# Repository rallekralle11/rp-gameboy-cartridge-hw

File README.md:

I had the idea to add the option to mount the USB port completely internally as well so it looks more "elegant".

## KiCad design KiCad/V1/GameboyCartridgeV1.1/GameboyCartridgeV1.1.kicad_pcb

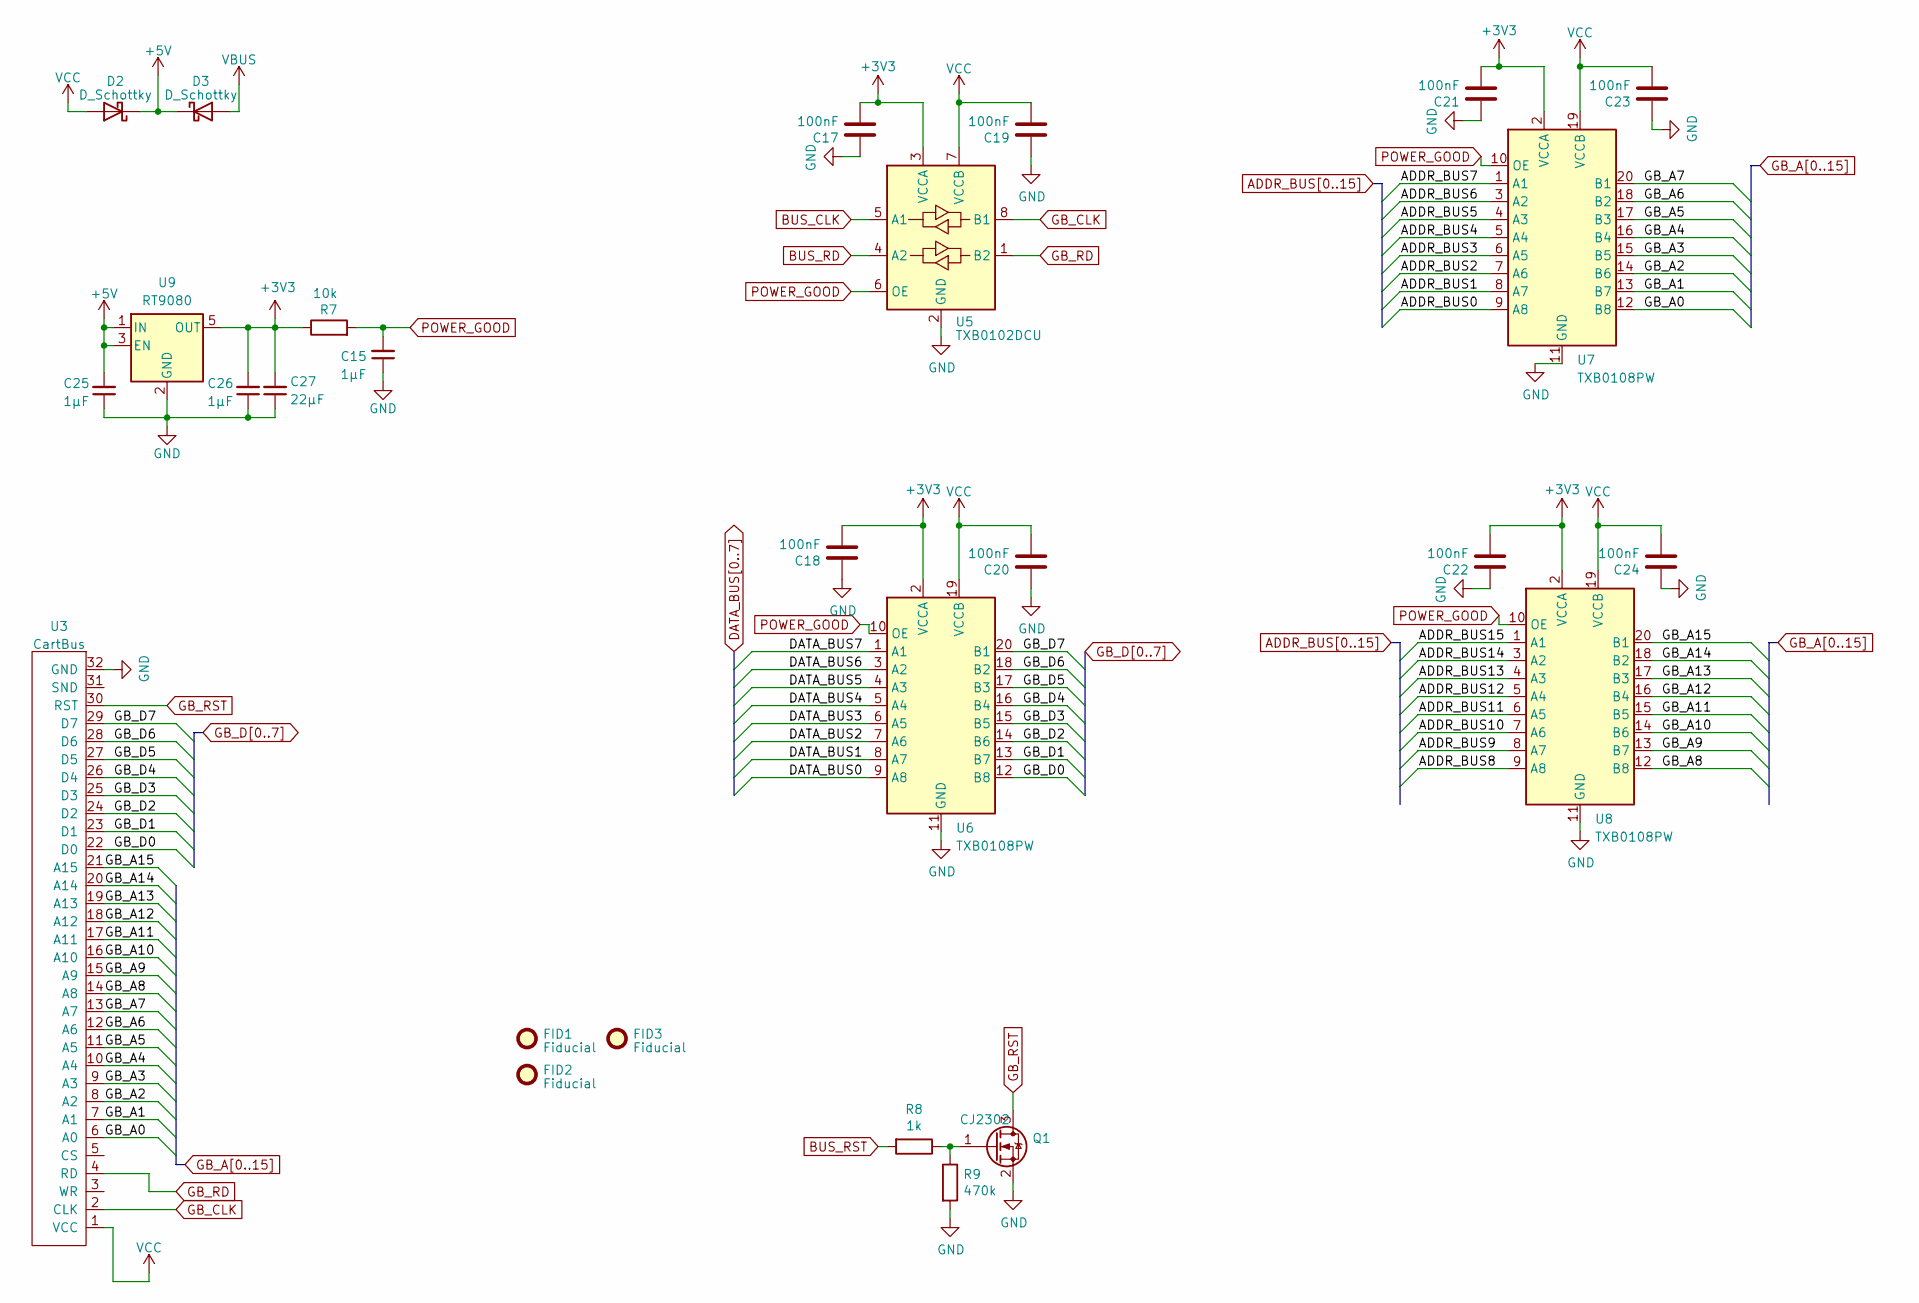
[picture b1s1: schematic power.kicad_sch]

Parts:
C15, C25, C26: 1µF; C_0603_1608Metric_Pad1.08x0.95mm_HandSolder
C17, C18, C19, C20, C21, C22, C23, C24: 100nF; C_0603_1608Metric_Pad1.08x0.95mm_HandSolder
C27: 22µF; C_0805_2012Metric
D2, D3: D_Schottky; D_SOD-323; LCSC C669022
FID1, FID2, FID3: Fiducial; Fiducial_1mm_Mask2mm
Q1: CJ2302; SOT-23_Handsoldering; LCSC C8548
R7: 10k; R_0603_1608Metric_Pad0.98x0.95mm_HandSolder
R8: 1k; R_0603_1608Metric_Pad0.98x0.95mm_HandSolder
R9: 470k; R_0603_1608Metric_Pad0.98x0.95mm_HandSolder
U3: CartBus; GameBoy_Cartridge_EdgeConnector
U5: TXB0102DCU; VSSOP-8_2.4x2.1mm_P0.5mm; LCSC C60709
U6, U7, U8: TXB0108PW; TSSOP-20_4.4x6.5mm_P0.65mm; LCSC C53406
U9: RT9080; SOT-23-5

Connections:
+3V3: C17.2, C18.2, C21.2, C22.2, C26.2, C27.2, R7.1, U5.3 (VCCA), U6.2 (VCCA), U7.2 (VCCA), U8.2 (VCCA), U9.5 (OUT); also elsewhere on the board
+5V: C25.2, D2.1 (K), D3.1 (K), U9.1 (IN), U9.3 (EN)
ADDR_BUS0: U7.9 (A8); also elsewhere on the board
ADDR_BUS1: U7.8 (A7); also elsewhere on the board
ADDR_BUS2: U7.7 (A6); also elsewhere on the board
ADDR_BUS3: U7.6 (A5); also elsewhere on the board
ADDR_BUS4: U7.5 (A4); also elsewhere on the board
ADDR_BUS5: U7.4 (A3); also elsewhere on the board
ADDR_BUS6: U7.3 (A2); also elsewhere on the board
ADDR_BUS7: U7.1 (A1); also elsewhere on the board
ADDR_BUS8: U8.9 (A8); also elsewhere on the board
ADDR_BUS9: U8.8 (A7); also elsewhere on the board
ADDR_BUS10: U8.7 (A6); also elsewhere on the board
ADDR_BUS11: U8.6 (A5); also elsewhere on the board
ADDR_BUS12: U8.5 (A4); also elsewhere on the board
ADDR_BUS13: U8.4 (A3); also elsewhere on the board
ADDR_BUS14: U8.3 (A2); also elsewhere on the board
ADDR_BUS15: U8.1 (A1); also elsewhere on the board
BUS_CLK: U5.5 (A1); also elsewhere on the board
BUS_RD: U5.4 (A2); also elsewhere on the board
BUS_RST: R8.2; also elsewhere on the board
DATA_BUS0: U6.9 (A8); also elsewhere on the board
DATA_BUS1: U6.8 (A7); also elsewhere on the board
DATA_BUS2: U6.7 (A6); also elsewhere on the board
DATA_BUS3: U6.6 (A5); also elsewhere on the board
DATA_BUS4: U6.5 (A4); also elsewhere on the board
DATA_BUS5: U6.4 (A3); also elsewhere on the board
DATA_BUS6: U6.3 (A2); also elsewhere on the board
DATA_BUS7: U6.1 (A1); also elsewhere on the board
GB_A0: U3.6 (A0), U7.12 (B8)
GB_A1: U3.7 (A1), U7.13 (B7)
GB_A2: U3.8 (A2), U7.14 (B6)
GB_A3: U3.9 (A3), U7.15 (B5)
GB_A4: U3.10 (A4), U7.16 (B4)
GB_A5: U3.11 (A5), U7.17 (B3)
GB_A6: U3.12 (A6), U7.18 (B2)
GB_A7: U3.13 (A7), U7.20 (B1)
GB_A8: U3.14 (A8), U8.12 (B8)
GB_A9: U3.15 (A9), U8.13 (B7)
GB_A10: U3.16 (A10), U8.14 (B6)
GB_A11: U3.17 (A11), U8.15 (B5)
GB_A12: U3.18 (A12), U8.16 (B4)
GB_A13: U3.19 (A13), U8.17 (B3)
GB_A14: U3.20 (A14), U8.18 (B2)
GB_A15: U3.21 (A15), U8.20 (B1)
GB_CLK: U3.2 (CLK~), U5.8 (B1)
GB_D0: U3.22 (D0), U6.12 (B8)
GB_D1: U3.23 (D1), U6.13 (B7)
GB_D2: U3.24 (D2), U6.14 (B6)
GB_D3: U3.25 (D3), U6.15 (B5)
GB_D4: U3.26 (D4), U6.16 (B4)
GB_D5: U3.27 (D5), U6.17 (B3)
GB_D6: U3.28 (D6), U6.18 (B2)
GB_D7: U3.29 (D7), U6.20 (B1)
GB_RD: U3.4 (RD), U5.1 (B2)
GB_RST: Q1.3 (D), U3.30 (RST)
GND: C15.1, C17.1, C18.1, C19.1, C20.1, C21.1, C22.1, C23.1, C24.1, C25.1, C26.1, C27.1, Q1.2 (S), R9.2, U3.32 (GND), U5.2 (GND), U6.11 (GND), U7.11 (GND), U8.11 (GND), U9.2 (GND); also elsewhere on the board
unnamed: Q1.1 (G), R8.1, R9.1
POWER_GOOD: C15.2, R7.2, U5.6 (OE), U6.10 (OE), U7.10 (OE), U8.10 (OE)
VBUS: D3.2 (A); also elsewhere on the board
VCC: C19.2, C20.2, C23.2, C24.2, D2.2 (A), U3.1 (VCC), U5.7 (VCCB), U6.19 (VCCB), U7.19 (VCCB), U8.19 (VCCB)

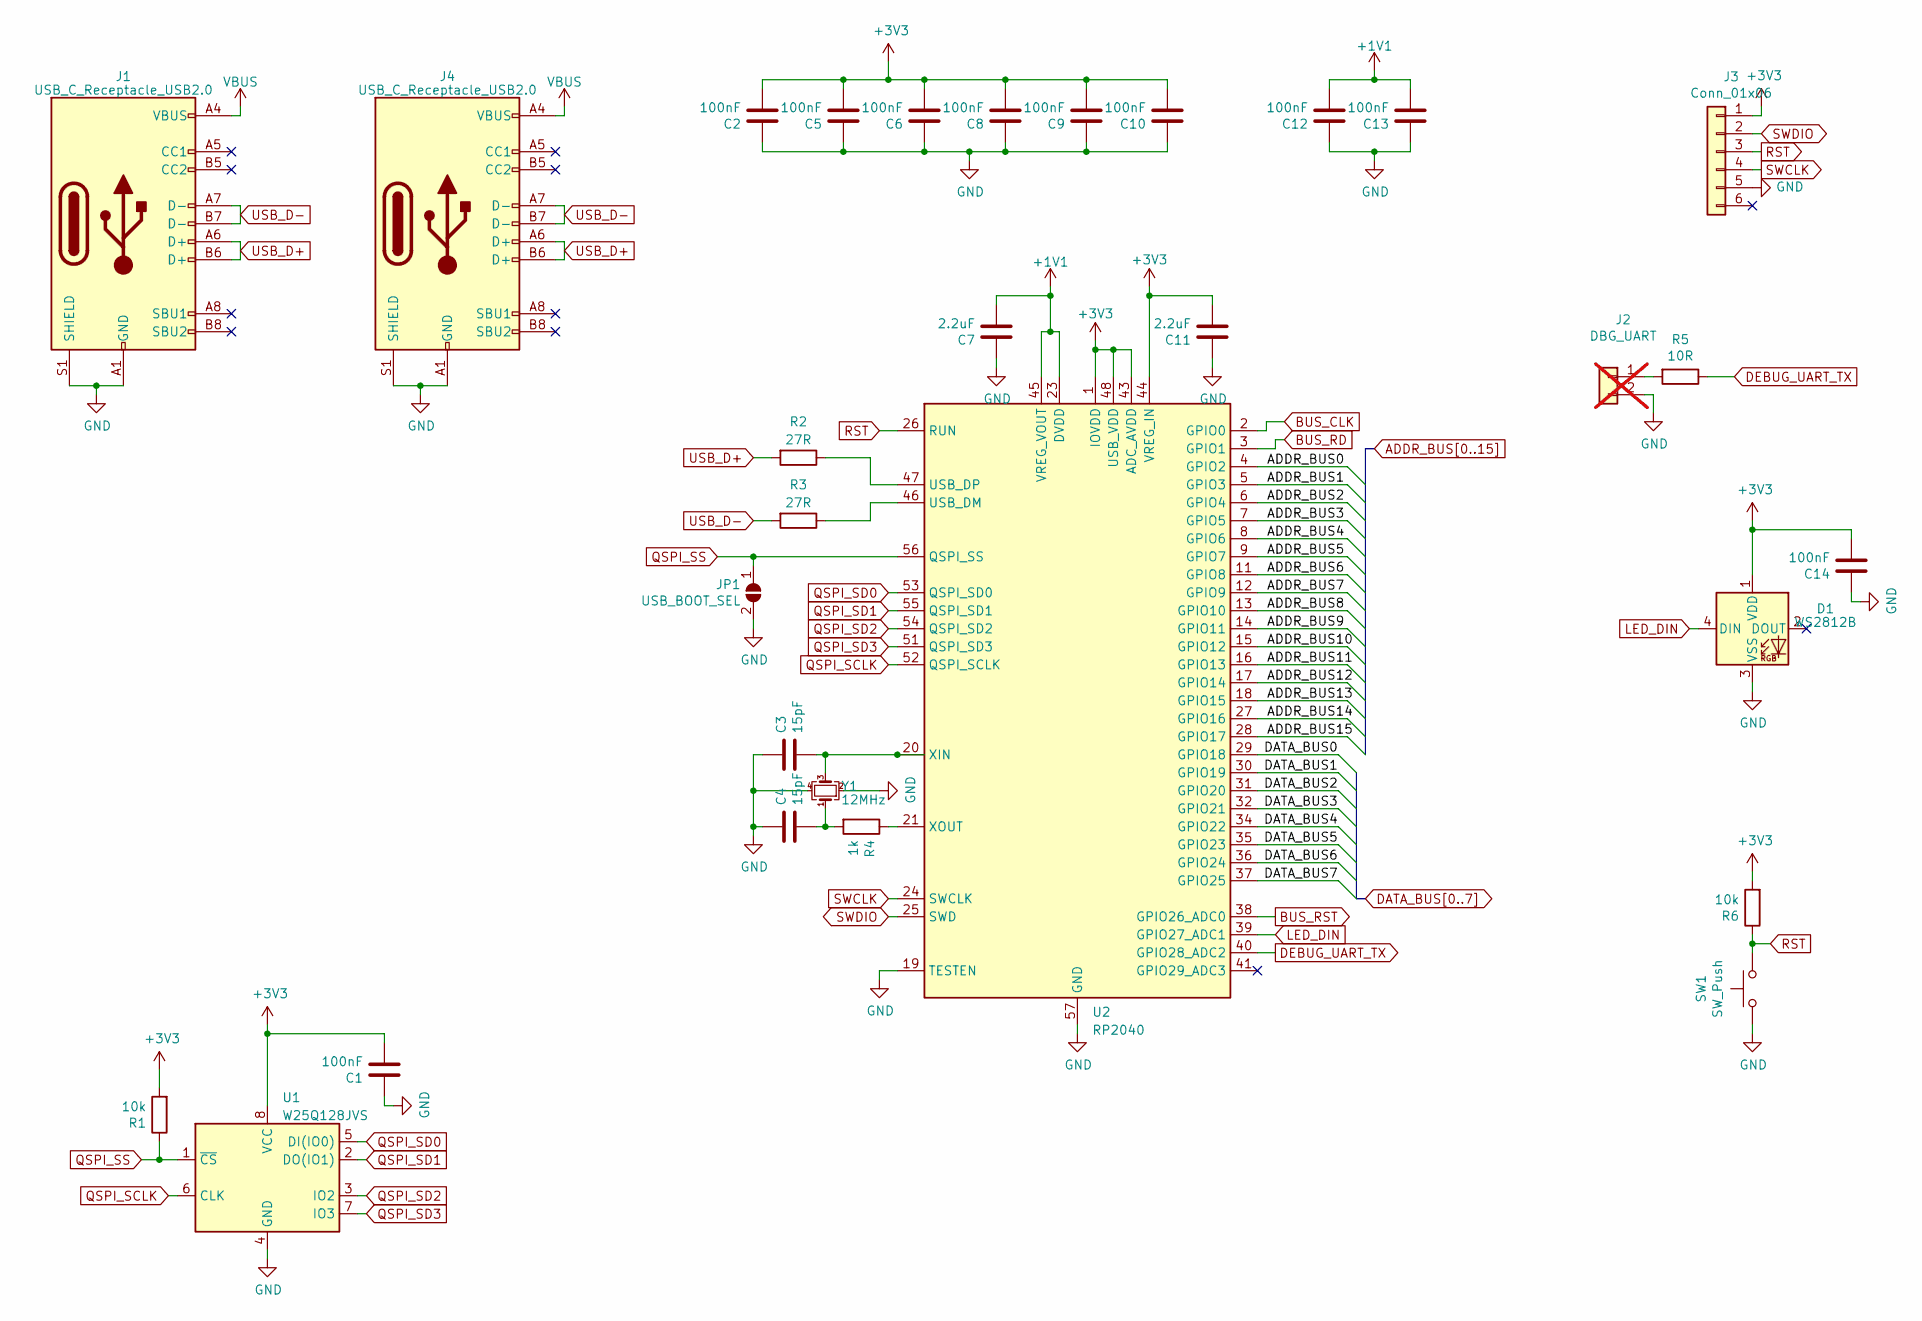
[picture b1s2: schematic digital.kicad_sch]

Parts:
C1, C2, C5, C6, C8, C9, C10, C12, C13, C14: 100nF; C_0603_1608Metric_Pad1.08x0.95mm_HandSolder
C3, C4: 15pF; C_0603_1608Metric_Pad1.08x0.95mm_HandSolder; LCSC C1644
C7, C11: 2.2uF; C_0603_1608Metric_Pad1.08x0.95mm_HandSolder
D1: WS2812B; LED_WS2812B-2020_PLCC4_2.0x2.0mm; LCSC C2761795
J1, J4: USB_C_Receptacle_USB2.0; USB_C_Receptacle_GCT_USB4105-xx-A_16P_TopMnt_Horizontal; LCSC C2927037
J2: DBG_UART; PinHeader_1x02_P2.54mm_Horizontal; not fitted
J3: Conn_01x06; Tag-Connect_TC2030-IDC-FP_2x03_P1.27mm_Vertical
JP1: USB_BOOT_SEL; SolderJumper-2_P1.3mm_Open_RoundedPad1.0x1.5mm
R1, R6: 10k; R_0603_1608Metric_Pad0.98x0.95mm_HandSolder
R2, R3: 27R; R_0603_1608Metric_Pad0.98x0.95mm_HandSolder
R4: 1k; R_0603_1608Metric_Pad0.98x0.95mm_HandSolder
R5: 10R; R_0603_1608Metric_Pad0.98x0.95mm_HandSolder
SW1: SW_Push; SW_Push_SPST_NO_Alps_SKRK; LCSC C2886898
U1: W25Q128JVS; SOIC-8_5.23x5.23mm_P1.27mm; LCSC C97521
U2: RP2040; QFN-56-1EP_7x7mm_P0.4mm_EP3.2x3.2mm; LCSC C2040
Y1: 12MHz; Crystal_SMD_TXC_7M-4Pin_3.2x2.5mm; LCSC C668845

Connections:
+1V1: C7.2, C12.2, C13.2, U2.23 (DVDD), U2.45 (VREG_VOUT), U2.50 (DVDD)
+3V3: C1.2, C2.2, C5.2, C6.2, C8.2, C9.2, C10.2, C11.2, C14.2, D1.1 (VDD), J3.1, R1.2, R6.2, U1.8 (VCC), U2.1 (IOVDD), U2.10 (IOVDD), U2.22 (IOVDD), U2.33 (IOVDD), U2.42 (IOVDD), U2.43 (ADC_AVDD), U2.44 (VREG_IN), U2.48 (USB_VDD), U2.49 (IOVDD); also elsewhere on the board
ADDR_BUS0: U2.4 (GPIO2); also elsewhere on the board
ADDR_BUS1: U2.5 (GPIO3); also elsewhere on the board
ADDR_BUS2: U2.6 (GPIO4); also elsewhere on the board
ADDR_BUS3: U2.7 (GPIO5); also elsewhere on the board
ADDR_BUS4: U2.8 (GPIO6); also elsewhere on the board
ADDR_BUS5: U2.9 (GPIO7); also elsewhere on the board
ADDR_BUS6: U2.11 (GPIO8); also elsewhere on the board
ADDR_BUS7: U2.12 (GPIO9); also elsewhere on the board
ADDR_BUS8: U2.13 (GPIO10); also elsewhere on the board
ADDR_BUS9: U2.14 (GPIO11); also elsewhere on the board
ADDR_BUS10: U2.15 (GPIO12); also elsewhere on the board
ADDR_BUS11: U2.16 (GPIO13); also elsewhere on the board
ADDR_BUS12: U2.17 (GPIO14); also elsewhere on the board
ADDR_BUS13: U2.18 (GPIO15); also elsewhere on the board
ADDR_BUS14: U2.27 (GPIO16); also elsewhere on the board
ADDR_BUS15: U2.28 (GPIO17); also elsewhere on the board
BUS_CLK: U2.2 (GPIO0); also elsewhere on the board
BUS_RD: U2.3 (GPIO1); also elsewhere on the board
BUS_RST: U2.38 (GPIO26_ADC0); also elsewhere on the board
DATA_BUS0: U2.29 (GPIO18); also elsewhere on the board
DATA_BUS1: U2.30 (GPIO19); also elsewhere on the board
DATA_BUS2: U2.31 (GPIO20); also elsewhere on the board
DATA_BUS3: U2.32 (GPIO21); also elsewhere on the board
DATA_BUS4: U2.34 (GPIO22); also elsewhere on the board
DATA_BUS5: U2.35 (GPIO23); also elsewhere on the board
DATA_BUS6: U2.36 (GPIO24); also elsewhere on the board
DATA_BUS7: U2.37 (GPIO25); also elsewhere on the board
DEBUG_UART_TX: R5.1, U2.40 (GPIO28_ADC2)
GND: C1.1, C2.1, C3.1, C4.1, C5.1, C6.1, C7.1, C8.1, C9.1, C10.1, C11.1, C12.1, C13.1, C14.1, D1.3 (VSS), J1.A1 (GND), J1.A12 (GND), J1.B1 (GND), J1.B12 (GND), J1.S1 (SHIELD), J2.2, J3.5, J4.A1 (GND), J4.A12 (GND), J4.B1 (GND), J4.B12 (GND), J4.S1 (SHIELD), JP1.2 (B), SW1.2, U1.4 (GND), U2.19 (TESTEN), U2.57 (GND), Y1.2, Y1.4; also elsewhere on the board
LED_DIN: D1.4 (DIN), U2.39 (GPIO27_ADC1)
unnamed: C4.2, R4.2, Y1.1
unnamed: J2.1, R5.2
unnamed: R3.1, U2.46 (USB_DM)
unnamed: R2.1, U2.47 (USB_DP)
unnamed: C3.2, U2.20 (XIN), Y1.3
unnamed: R4.1, U2.21 (XOUT)
QSPI_SCLK: U1.6 (CLK), U2.52 (QSPI_SCLK)
QSPI_SD0: U1.5 (DI(IO0)), U2.53 (QSPI_SD0)
QSPI_SD1: U1.2 (DO(IO1)), U2.55 (QSPI_SD1)
QSPI_SD2: U1.3 (IO2), U2.54 (QSPI_SD2)
QSPI_SD3: U1.7 (IO3), U2.51 (QSPI_SD3)
QSPI_SS: JP1.1 (A), R1.1, U1.1 (~CS), U2.56 (QSPI_SS)
RST: J3.3, R6.1, SW1.1, U2.26 (RUN)
SWCLK: J3.4, U2.24 (SWCLK)
SWDIO: J3.2, U2.25 (SWD)
USB_D+: J1.A6 (D+), J1.B6 (D+), J4.A6 (D+), J4.B6 (D+), R2.2
USB_D-: J1.A7 (D-), J1.B7 (D-), J4.A7 (D-), J4.B7 (D-), R3.2
VBUS: J1.A4 (VBUS), J1.A9 (VBUS), J1.B4 (VBUS), J1.B9 (VBUS), J4.A4 (VBUS), J4.A9 (VBUS), J4.B4 (VBUS), J4.B9 (VBUS); also elsewhere on the board

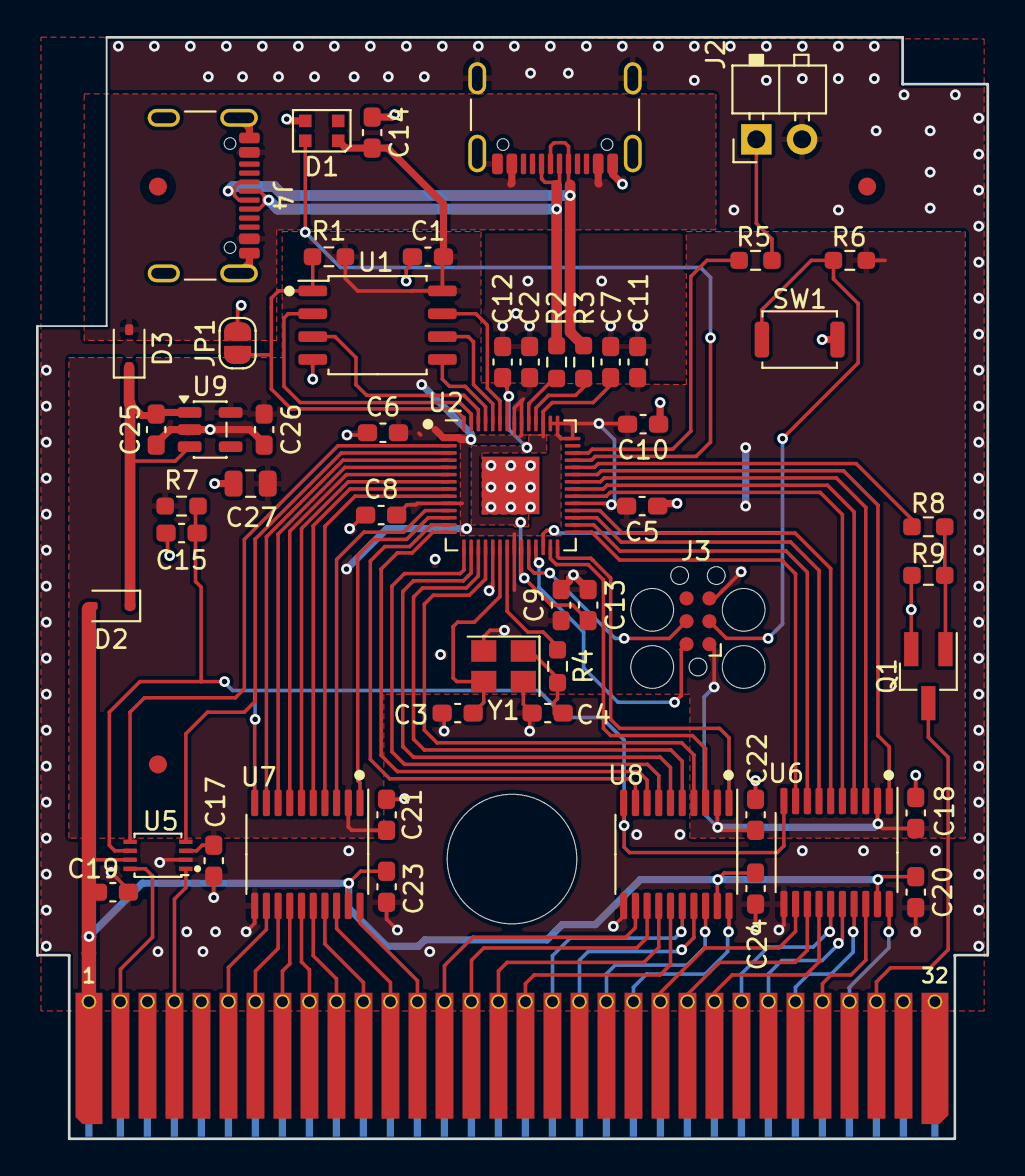
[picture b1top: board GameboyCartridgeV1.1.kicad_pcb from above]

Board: 2 copper layers, 52.8 x 61.2 mm, 57 parts (0 on the bottom side), 81 nets.

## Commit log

2025-07-16 Upload V2.1
2025-10-24 main changes
2025-10-24 gerbers
2025-10-24 picture
2025-10-24 usb port placement
